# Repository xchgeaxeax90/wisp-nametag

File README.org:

#+title: Wisp Light-up Nametag

[[./img/nametag_2.0.jpg]]

This repository contains the PCB design and software for the light up
nametag I will be giving out at Offkai Expo 2026. 

* Usage
** Battery

*NOTE: Please be very careful to insert the battery with the correct polarity in the battery holder. Failure to do so may result in destruction of the device*

The Badge is powered by a 1.5V AAA battery. While I have not tested it, it should be compatible with rechargable AAA cells or lithium rechargable cells, provided the battery voltage is below 3 volts.

While powered down, the badge draws a small amount of current from the battery at all times. When storing the badge for long periods of time (weeks-months), please remove the battery so as to avoid draining the battery or causing it to leak.

*** User Interface

- Tap the button on the bottom right to change the blink pattern
- Press and hold the button on the bottom right for about 2 seconds, then release to enter brightness mode. The LEDs will stop blinking and remain on continuously
- When in brightness mode, tap the button to change the brightness
- To exit brightness mode, press and hold the button for about 2 seconds, then release. The LEDs should begin blinking again
- To power off the device, press and hold the button until the LEDs turn off
- To power the device back on, tap the button again

* Manufacture

** Hardware
The PCBs I made were ordered from [[https://jlcpcb.com][JLCPCB]], through their PCB Assembly
service. The design files under the [[https://github.com/xchgeaxeax90/wisp-nametag/releases/tag/v2.0][v2.0 Manufacturing Files]] release
can be uploaded to JLCPCB's automatic quote system to order either
bare PCBs or assembled boards.

*** Parts

The Bill of Materials is below. When viewing the BOM from Kicad, the JLCPCB/LCSC part ids should be taken as the reference, some of the part numbers in the schematic are incorrect

| Part Name            | Designator              | Comment                                                                |
|----------------------+-------------------------+------------------------------------------------------------------------|
| TZ-P2-0603GTCS1-0.6T | D9,D10,D11,D12,D13,D14  | 0603 SMD LED – Emerald Green 520nm                                     |
| TS-1088-AR02016      | SW1                     | 3.9x3.0mm SPST Momentary Button                                        |
| CL10A226MQ8NRNC      | C1                      | 0603 22uf ceramic capacitor                                            |
| MPL2016S2R2MHT       | L1                      | 0806 2.2 uH inductor                                                   |
| BL8536CB3TR36        | U2                      | 0.9V-3.3V Ultra Low Voltage Boost Converter                            |
| 0603WAF470JT5E       | R1,R2                   | 0603 47 Ohm Resistor                                                   |
| STC8H1K08-36I-QFN20  | U3                      | STC8H1K08 24MHz microcontroller                                        |
| CL05B104KO5NNNC      | C2                      | 0402 100nF Capacitor                                                   |
| LTST-C190KFKT        | D1,D2,D3,D4,D5,D6,D7,D8 | 0603 SMD LED – Orange 605nm                                            |
| SMLD12E3N1WT86       | D15,D16                 | 0603 SMD LED – Cyan 496nm                                              |
| 0603WAF3000T5E       | R3,R4,R5,R6,R7,R8       | 0603 300 Ohm Resistor                                                  |
| 2466                 | BT1                     | AAA Battery Holder (not included in JLCPCB quote, hand solder on back) |

Note: If manufacturing this yourself, consider using the
SMLD12E2N1WT86 505nm Blue-Green LED in place of the 520 Emerald Green
LED. It looks much closer to mint green, but is much more difficult
and expensive to source

** Software

The software loaded on the badges I gave (or will give) out can be
found at the [[https://github.com/xchgeaxeax90/wisp-nametag/releases/tag/v2.0-software][v2.0 Software]] release. This contains the entire source
code as well as prebuilt binaries that can be loaded directly onto the
boards.

*** Programming

The microcontroller can be programmed using a 3.3V USB to UART cable and the [[https://github.com/grigorig/stcgal][STCGal programmer software]].

1. Completely remove power from the board. The board cannot just be put to sleep using the button, it must be entirely powered off, with the battery removed
2. Connect the microcontroller's TX and RX pins to the UART. These pins can be found on the programming header on the bottom left of the PCB when viewed from the back. If you're good, you can likely do this by just shoving pins in the holes instead of soldering them in place.
3. Start =stcgal=, replacing =/dev/ttyUSB0= with your USB to UART's serial port device 
   
#+BEGIN_SRC bash
  stcgal -p /dev/ttyUSB0 -P stc8g --trim 24000 path/to/app.hex
#+END_SRC

4. Power on the board - I like to use alligator clips to clip directly on to the battery terminals, but you can also just insert the battery

5. The programmer should automatically begin downloading the code to the microcontroller

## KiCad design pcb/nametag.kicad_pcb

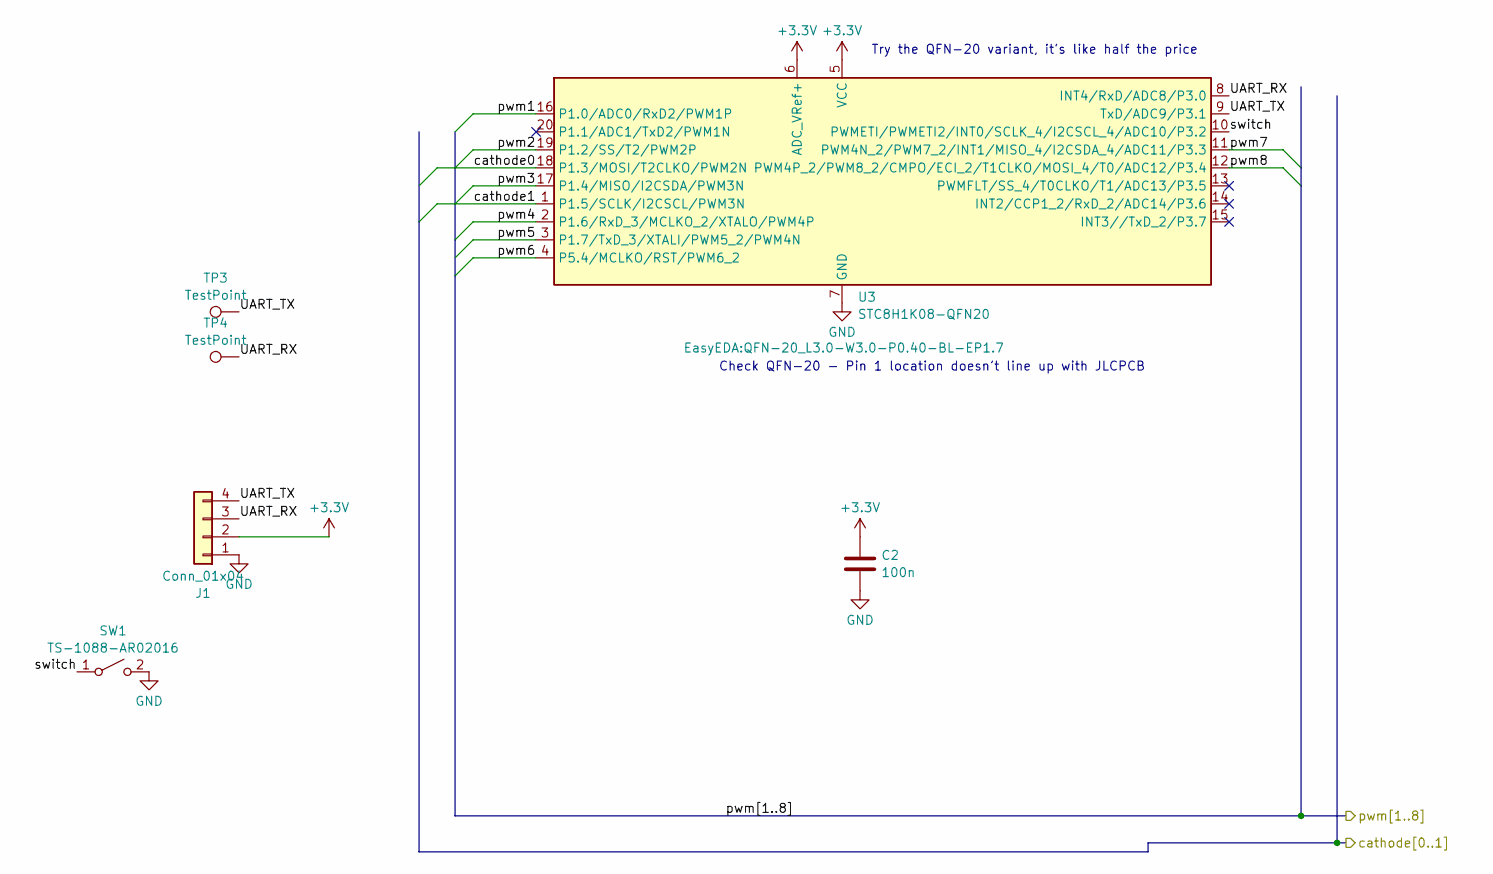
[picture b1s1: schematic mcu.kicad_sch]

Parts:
C2: 100n; C_0402_1005Metric; LCSC C1525
J1: Conn_01x04; PinSocket_1x04_P2.54mm_Vertical
SW1: TS-1088-AR02016; SW-SMD_L3.9-W3.0-P4.45
TP3, TP4: TestPoint; TestPoint_Pad_D1.0mm
U3: STC8H1K08-QFN20; QFN-20_L3.0-W3.0-P0.40-BL-EP1.7; LCSC C915674

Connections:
+3.3V: C2.1, J1.2, U3.5 (VCC), U3.6 (ADC_VRef+); also elsewhere on the board
/Mcu/UART_RX: J1.3, TP4.1 (1_1), U3.8 (INT4/RxD/ADC8/P3.0)
/Mcu/UART_TX: J1.4, TP3.1 (1_1), U3.9 (TxD/ADC9/P3.1)
/Mcu/cathode0: U3.18 (P1.3/MOSI/T2CLKO/PWM2N); also elsewhere on the board
/Mcu/cathode1: U3.1 (P1.5/SCLK/I2CSCL/PWM3N); also elsewhere on the board
/Mcu/pwm1: U3.16 (P1.0/ADC0/RxD2/PWM1P); also elsewhere on the board
/Mcu/pwm2: U3.19 (P1.2/SS/T2/PWM2P); also elsewhere on the board
/Mcu/pwm3: U3.17 (P1.4/MISO/I2CSDA/PWM3N); also elsewhere on the board
/Mcu/pwm4: U3.2 (P1.6/RxD_3/MCLKO_2/XTALO/PWM4P); also elsewhere on the board
/Mcu/pwm5: U3.3 (P1.7/TxD_3/XTALI/PWM5_2/PWM4N); also elsewhere on the board
/Mcu/pwm6: U3.4 (P5.4/MCLKO/RST/PWM6_2); also elsewhere on the board
/Mcu/pwm7: U3.11 (PWM4N_2/PWM7_2/INT1/MISO_4/I2CSDA_4/ADC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); also elsewhere on the board
/Mcu/pwm8: U3.12 (PWM4P_2/PWM8_2/CMPO/ECI_2/T1CLKO/MOSI_4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); also elsewhere on the board
/Mcu/switch: SW1.1 (A), U3.10 (PWMETI/PWMETI2/INT0/SCLK_4/I2CSCL_4/ADC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)
GND: C2.2, J1.1, SW1.2 (B), U3.7 (GND), U3.21 (EP); also elsewhere on the board

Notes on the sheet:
Check QFN-20 - Pin 1 location doesn't line up with JLCPCB
Try the QFN-20 variant, it's like half the price

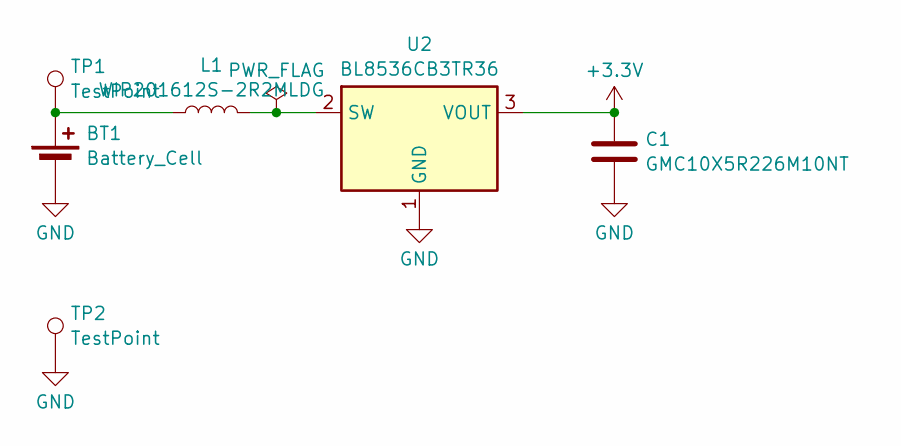
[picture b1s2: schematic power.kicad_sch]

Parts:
BT1: Battery_Cell; BatteryHolder_Keystone_2466_1xAAA
C1: GMC10X5R226M10NT; C_0603_1608Metric; LCSC C59461
L1: WIP201612S-2R2MLDG; L0806; LCSC C42215
TP1, TP2: TestPoint; TestPoint_Pad_D1.0mm
U2: BL8536CB3TR36; SOT-23-3_L2.9-W1.6-P1.90-LS2.8-BR

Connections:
+3.3V: C1.1, U2.3 (VOUT); also elsewhere on the board
GND: BT1.2 (-), C1.2, TP2.1 (1_1), U2.1 (GND); also elsewhere on the board
unnamed: BT1.1 (+), L1.1, TP1.1 (1_1)
unnamed: L1.2, U2.2 (SW)

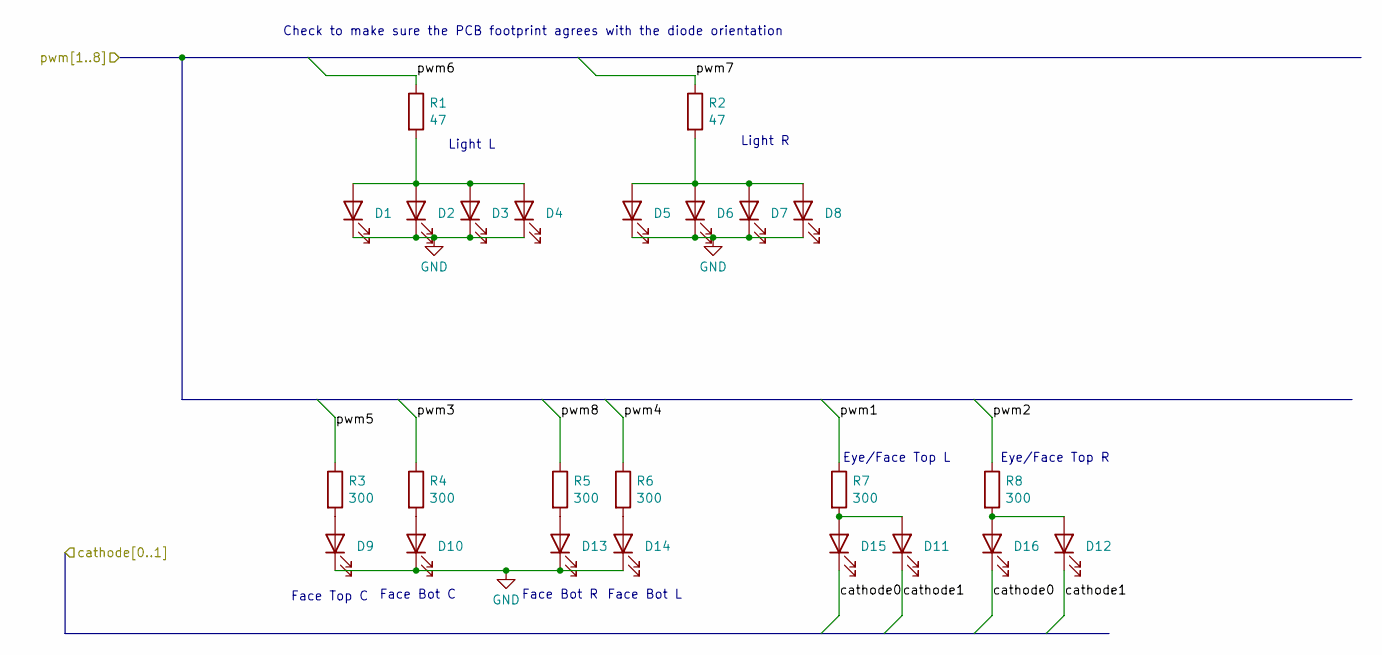
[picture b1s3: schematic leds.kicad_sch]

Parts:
D1, D2, D3, D4, D5, D6, D7, D8: LTST-C190KFKT; LED_0603_1608Metric; LCSC C157740
D9, D10, D11, D12, D13, D14: SMLD12E3N1WT86; LED_0603_1608Metric; LCSC C779453
D15, D16: SMLD12E2N1WT86; LED_0603_1608Metric; LCSC C2846641
R1, R2: 47; R_0603_1608Metric; LCSC C23182
R3, R4, R5, R6, R7, R8: 300; R_0603_1608Metric; LCSC C23025

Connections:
/Mcu/cathode0: D15.1 (K), D16.1 (K); also elsewhere on the board
/Mcu/cathode1: D11.1 (K), D12.1 (K); also elsewhere on the board
/Mcu/pwm1: R7.1; also elsewhere on the board
/Mcu/pwm2: R8.1; also elsewhere on the board
/Mcu/pwm3: R4.1; also elsewhere on the board
/Mcu/pwm4: R6.1; also elsewhere on the board
/Mcu/pwm5: R3.1; also elsewhere on the board
/Mcu/pwm6: R1.1; also elsewhere on the board
/Mcu/pwm7: R2.1; also elsewhere on the board
/Mcu/pwm8: R5.1; also elsewhere on the board
GND: D1.1 (K), D2.1 (K), D3.1 (K), D4.1 (K), D5.1 (K), D6.1 (K), D7.1 (K), D8.1 (K), D9.1 (K), D10.1 (K), D13.1 (K), D14.1 (K); also elsewhere on the board
unnamed: D1.2 (A), D2.2 (A), D3.2 (A), D4.2 (A), R1.2
unnamed: D5.2 (A), D6.2 (A), D7.2 (A), D8.2 (A), R2.2
unnamed: D9.2 (A), R3.2
unnamed: D10.2 (A), R4.2
unnamed: D11.2 (A), D15.2 (A), R7.2
unnamed: D12.2 (A), D16.2 (A), R8.2
unnamed: D13.2 (A), R5.2
unnamed: D14.2 (A), R6.2

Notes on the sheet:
Face Bot L
Eye/Face Top R
Light L
Light R
Face Bot C
Check to make sure the PCB footprint agrees with the diode orientation
Eye/Face Top L
Face Bot R
Face Top C

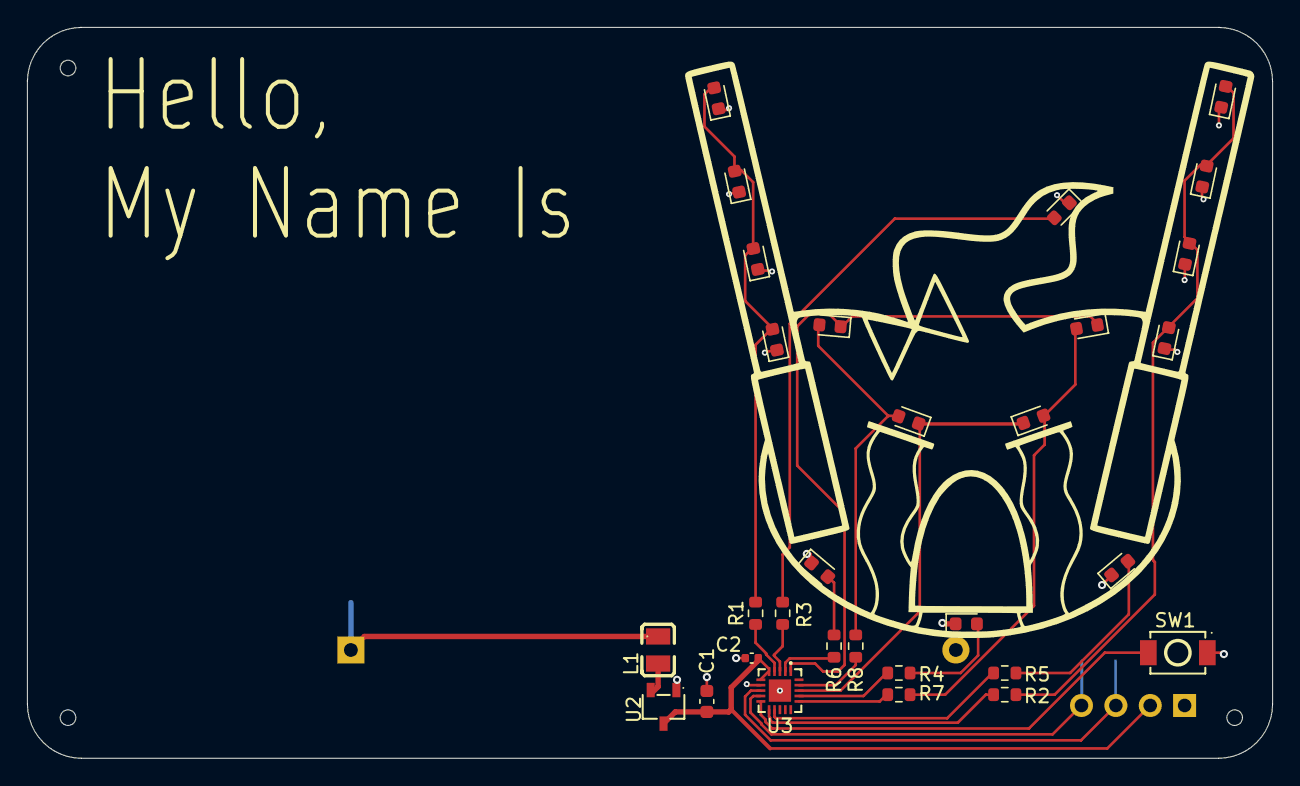
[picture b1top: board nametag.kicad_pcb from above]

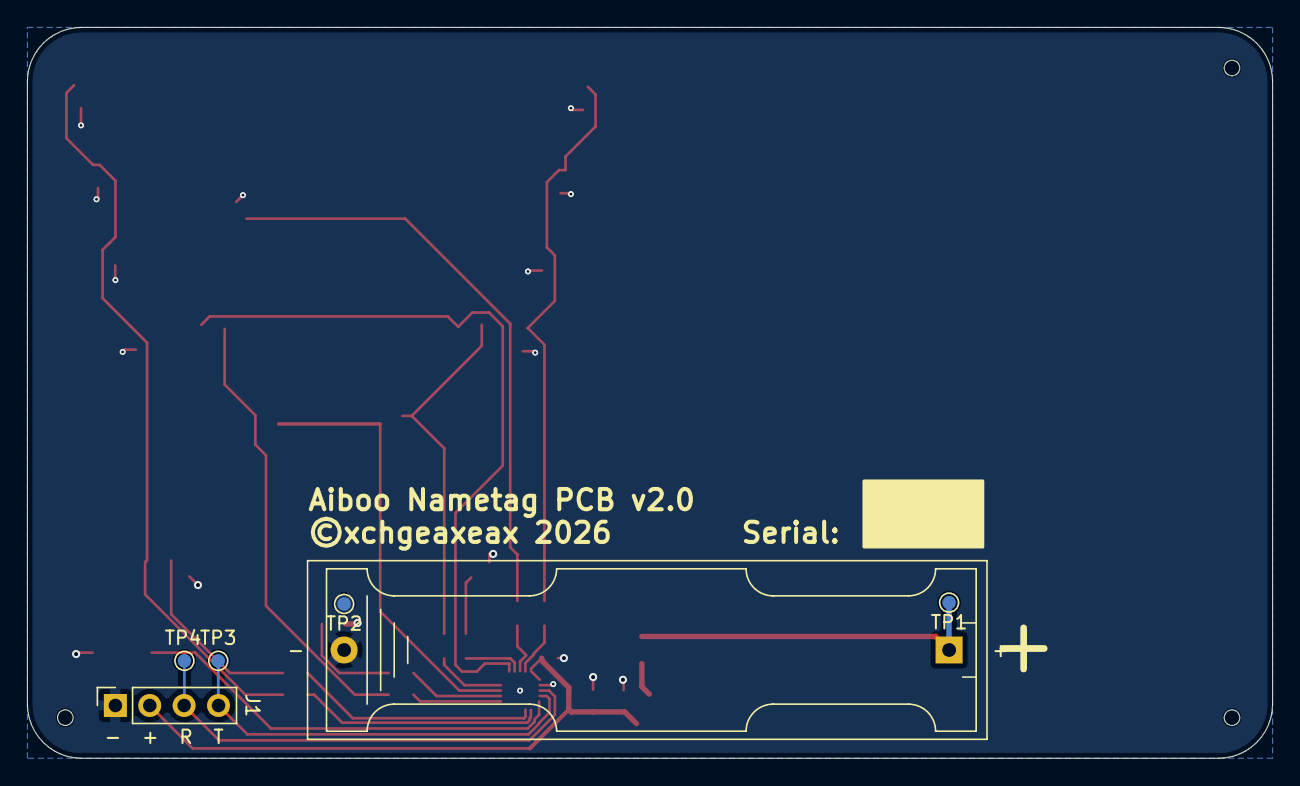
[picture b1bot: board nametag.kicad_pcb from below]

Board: 2 copper layers, 92.0 x 54.0 mm, 39 parts (6 on the bottom side), 25 nets.

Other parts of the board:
HO1, HO2, HO3: JLC PCBA Mounting Hole

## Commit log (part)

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2025-01-10 Swap to STC8H1K08 and work on JLCPCB assembly support
2026-05-30 More edits to PCB design
    - Change a couple of parts - voltage regulator - to use LCSC parts
    - Increase width of the nametag PCB
    - redo layout a bit
2026-05-30 Move old avr source code to its own folder
2026-05-30 Import FwLib_STC8, add demo code
2026-05-30 Create a hello world blinky on the stc8
2026-05-30 Enable all PWM channels on the device
2026-05-30 Remove most of the HAL calls in PWM setup
    Each HAL call is wrapped in SFRX_ON() and SFRX_OFF() - this uses a
    considerable amount of extra memory
2026-05-30 Enable timer 2 interrupt
2026-05-30 Update PCB to reflect PWM pin assignments
2026-05-31 Split out peripheral setup into separate files. Test deep sleep
2026-05-31 Update PCB with new naming of PWM channels
2026-05-31 Start fleshing out skeleton of old code
2026-05-31 Get basic PWM animation working
2026-05-31 Get most of the state machine working
2026-05-31 Get LED multiplexing working
2026-05-31 Synchronize PWM setting updates to the cathode multiplexing
2026-05-31 Attempt to get sleep working, the only way to make it restart is a software reset
2026-05-31 Some size reductions?
2026-06-01 Increase breathe animation resolution
2026-06-03 Small changes for manufacturability
2026-06-05 Reduce clock frequency to 1MHz
2026-06-06 Try swapping to a qfn part instead of tssop-20
2026-06-07 Add JLC PCBA Mounting holes
2026-06-07 Enlarge the PCB a bit
2026-06-07 Update footprints from LCSC EasyEDA Library
2026-06-07 Redo some of the layout, move button
2026-06-10 Submit files to JLCPCB for manufacture
2026-06-13 Add debug prints, fix issue with off animation
2026-06-13 Fix sleep mode current issue
2026-06-13 Fix some bugs in the avr version, maybe reduce power consumption?
2026-06-14 Potentially fix bug in the avr sleep entry
2026-06-14 I think fix some potential bugs?
2026-06-18 Fixup pin assignments to match the qfn pcb pinout
2026-06-18 Don't perform a reset after deep sleep
2026-06-18 Hack in a scale for the green leds to tame them a bit
2026-06-19 Create new twinkle animation
2026-06-19 Rework makefile, add argument to scale the green LEDs
2026-06-19 Have both avr/stc8 share the same animation definitions

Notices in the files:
pcb/nametag.kicad_pcb:
©xchgeaxeax 2026
